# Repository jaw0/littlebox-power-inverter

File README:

google sponsored a contest, [the little box challenge,](https://www.littleboxchallenge.com)
to design a small, efficient, 2kVA power inverter.

this is what I came up with. it did not win.

* * * * * * * * WARNING * * * * * * * *

This device contains potentially lethal voltages.

This device does not comply with consumer grade
electrical safety requirements.

DO NOT USE OR BUILD THIS UNLESS YOU ARE FAMILIAR WITH
THE SAFETY PRECAUTIONS FOR WORKING WITH HIGH VOLTAGE.

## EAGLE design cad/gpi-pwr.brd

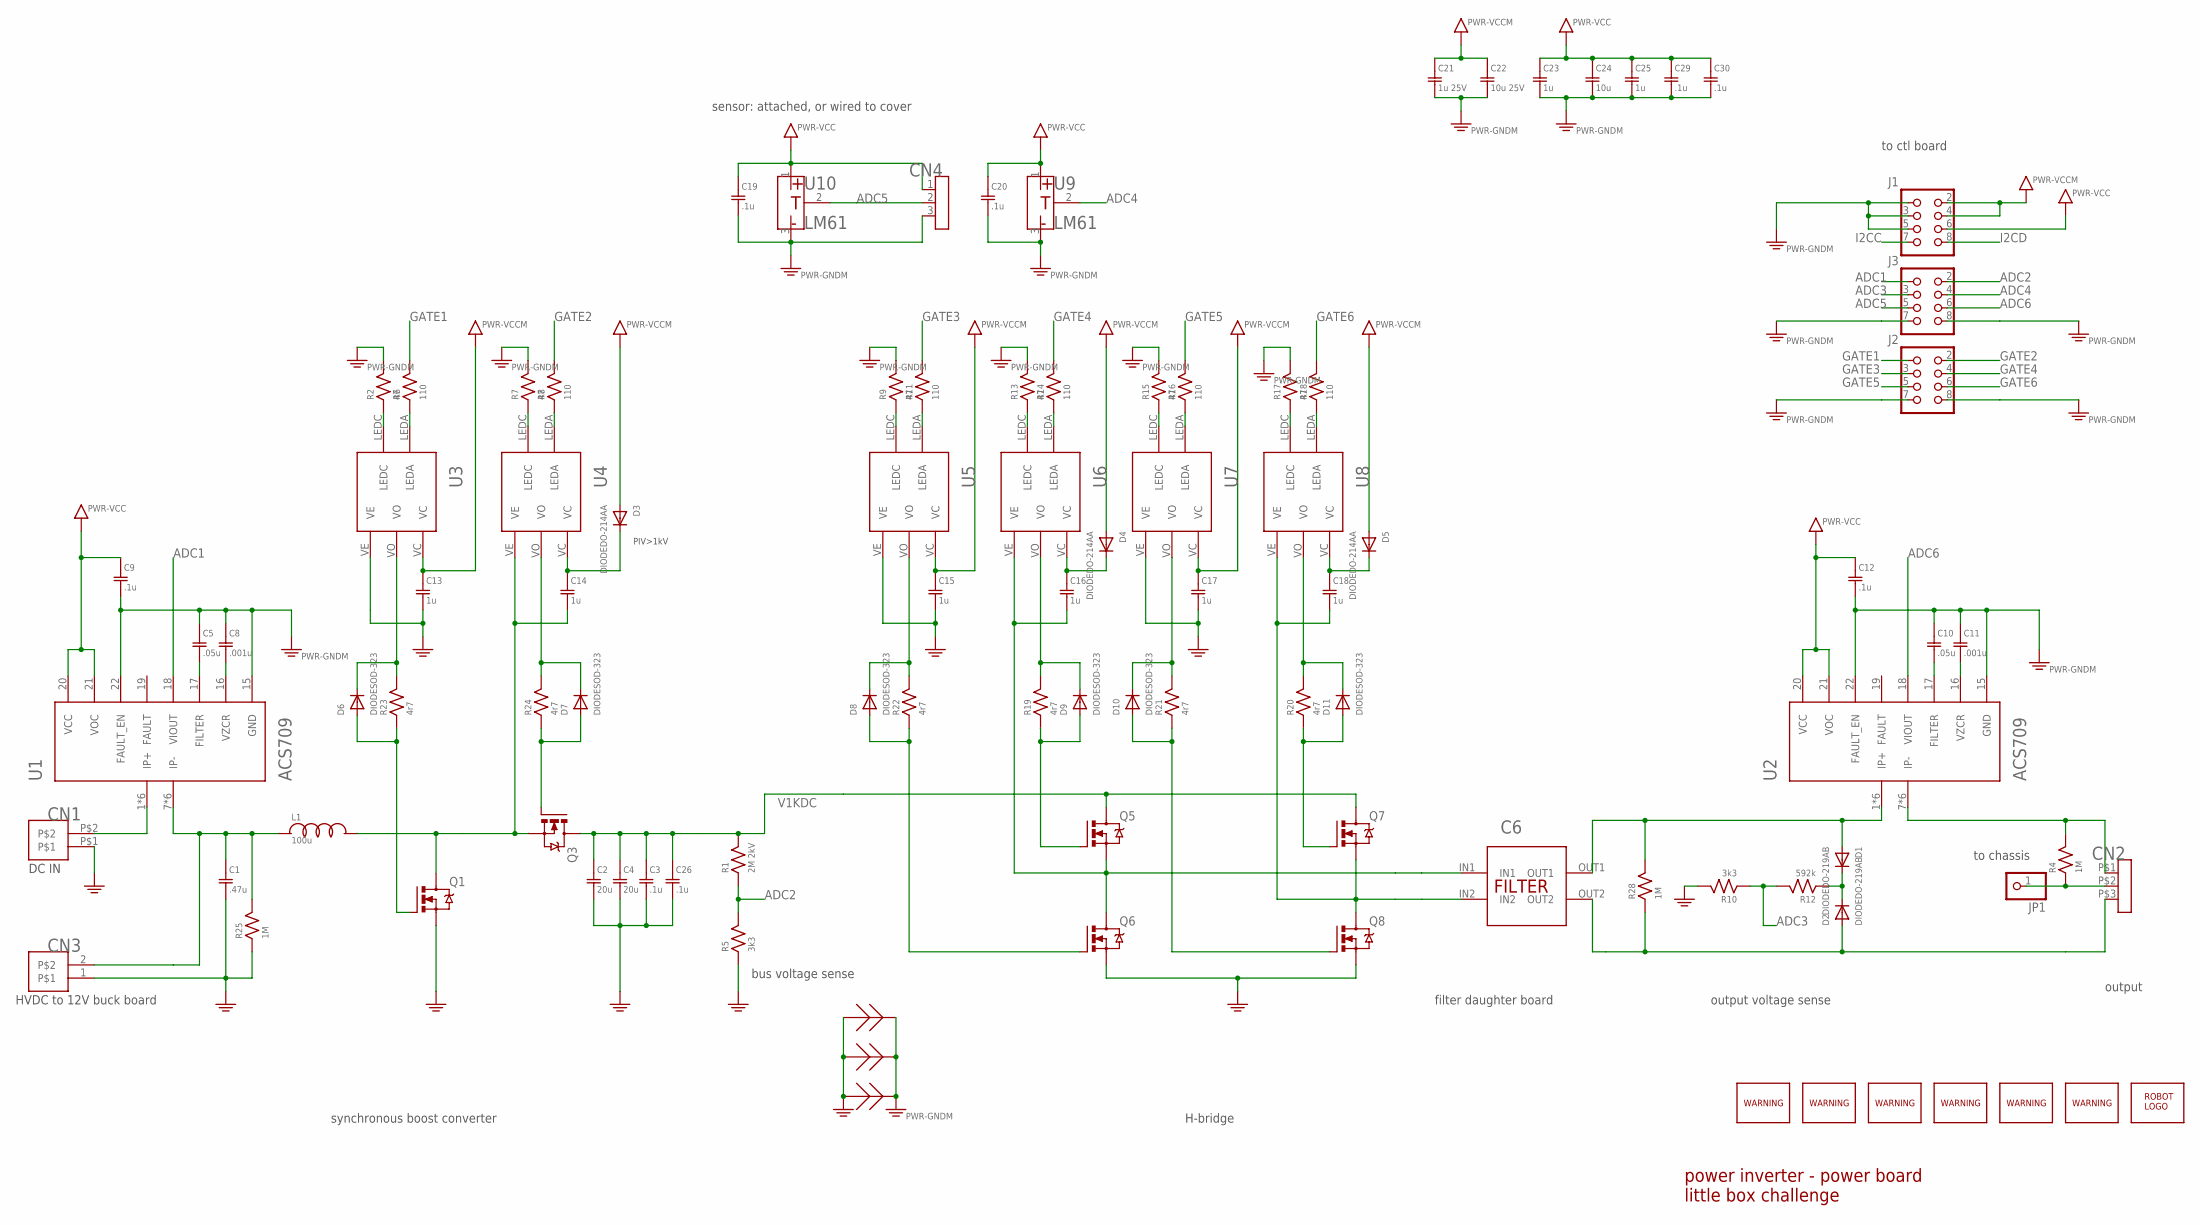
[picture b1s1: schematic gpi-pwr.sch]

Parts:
C1: .47u; R46KI333000N1M
C2, C4: 20u; MKP1848S62010JY5F
C3, C26: .1u; SMD2220
C5, C10: .05u; SMD0603
C6: FILTER; FILTER-B4R0
C8, C11: .001u; SMD0603
C9, C12, C19, C20, C29, C30: .1u; SMD0603
C13, C14, C15, C16, C17, C18, C23, C25: 1u; SMD0603
C21: 1u 25V; SMD0603
C22: 10u 25V; SMD0603
C24: 10u; SMD0603
CN1: HEADER-1X2; CONN-10AWG-2
CN2: HEADER-3X1; CONN-10AWG-3
CN3: HEADER-1X2.4; HEADER-1X2-THM-WIDE
CN4: HEADER-3X12MM; HEADER-3X1-2SMD
D1, D2: DIODEDO-219AB; DO-219AB
D3, D4, D5: DIODEDO-214AA; DO-214AA
D6, D7, D8, D9, D10, D11: DIODESOD-323; SOD-323
J1, J2, J3: HEADER-2X4; HEADER-2X04
JP1: PINHD-1X1; 1X01
L1: 100u; AIRD03
Q1, Q3, Q5, Q6, Q7, Q8: C2M0160120D; TO-247-3-DOWN
R1: 2M 2kV; SMD2512
R2, R7, R9, R13, R15, R17: 47; SMD0603
R4, R25, R28: 1M; SMD1206
R5, R10: 3k3; SMD0603
R6, R8, R11, R14, R16, R18: 110; SMD0603
R12: 592k; SMD1206
R19, R20, R21, R22, R23, R24: 4r7; SMD0508
U1, U2: ACS709; QSOP24
U3, U4, U5, U6, U7, U8: ACPL-P346P346; ACPL-P346
U9, U10: LM61; SOT-23
U$1: ROBOTMAN-LOGO
U$2, U$3, U$4, U$5, U$6, U$7: SYMBOL-WARNING
Z1, Z2, Z3: SHORT

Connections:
ADC1: J3.1, U1.18 (VIOUT)
ADC2: J3.2, R1.P$1, R5.2
ADC3: J3.3, R10.1, R12.2
ADC4: J3.4, U9.2 (OUT)
ADC5: CN4.2, J3.5, U10.2 (OUT)
ADC6: J3.6, U2.18 (VIOUT)
GATE1: J2.1, R6.2
GATE2: J2.2, R8.2
GATE3: J2.3, R11.2
GATE4: J2.4, R14.2
GATE5: J2.5, R16.2
GATE6: J2.6, R18.2
GND: C1.P$2, C2.2A, C2.2B, C3.P$2, C4.2A, C4.2B, C13.2, C15.2, C17.2, C26.P$2, CN1.P$1, CN3.1, Q1.3 (S), Q6.3 (S), Q8.3 (S), R5.1, R10.2, R25.1, U3.VE, U5.VE, U7.VE, Z1.P$1, Z2.P$1, Z3.P$1
GNDM: C5.1, C8.1, C9.2, C10.1, C11.1, C12.2, C19.2, C20.2, C21.2, C22.2, C23.2, C24.2, C25.2, C29.2, C30.2, CN4.3, J1.1, J1.3, J1.5, J2.7, J2.8, J3.7, J3.8, R2.2, R7.2, R9.2, R13.2, R15.2, R17.2, U1.15 (GND), U1.22 (FAULT_EN), U2.15 (GND), U2.22 (FAULT_EN), U9.3 (G), U10.3 (G), Z1.P$2, Z2.P$2, Z3.P$2
I2CC: J1.7
I2CD: J1.8
unnamed: CN1.P$2, U1.1 (IP+), U1.2 (IP+), U1.3 (IP+), U1.4 (IP+), U1.5 (IP+), U1.6 (IP+)
unnamed: D9.C, R19.P$2, U6.VO
unnamed: C14.2, L1.P$2, Q1.2 (D), Q3.3 (S), U4.VE
unnamed: D6.A, Q1.1 (G), R23.P$1
unnamed: D6.C, R23.P$2, U3.VO
unnamed: C1.P$1, CN3.2, L1.P$1, R25.2, U1.7 (IP-), U1.8 (IP-), U1.9 (IP-), U1.10 (IP-), U1.11 (IP-), U1.12 (IP-)
unnamed: D1.C, D2.C, R12.1
unnamed: CN2.P$1 (1), R4.2, U2.7 (IP-), U2.8 (IP-), U2.9 (IP-), U2.10 (IP-), U2.11 (IP-), U2.12 (IP-)
unnamed: CN2.P$2 (2), JP1.1, R4.1
unnamed: C5.2, U1.17 (FILTER)
unnamed: C8.2, U1.16 (VZCR)
unnamed: C10.2, U2.17 (FILTER)
unnamed: C6.IN1, C16.2, Q5.3 (S), Q6.2 (D), U6.VE
unnamed: C6.IN2, C18.2, Q7.3 (S), Q8.2 (D), U8.VE
unnamed: C11.2, U2.16 (VZCR)
unnamed: C14.1, D3.C, U4.VC
unnamed: D9.A, Q5.1 (G), R19.P$1
unnamed: D8.A, Q6.1 (G), R22.P$1
unnamed: D10.A, Q8.1 (G), R21.P$1
unnamed: D11.A, Q7.1 (G), R20.P$1
unnamed: R2.1, U3.LEDC
unnamed: C6.OUT1, D1.A, R28.2, U2.1 (IP+), U2.2 (IP+), U2.3 (IP+), U2.4 (IP+), U2.5 (IP+), U2.6 (IP+)
unnamed: C6.OUT2, CN2.P$3 (3), D2.A, R28.1
unnamed: C16.1, D4.C, U6.VC
unnamed: R6.1, U3.LEDA
unnamed: C18.1, D5.C, U8.VC
unnamed: R7.1, U4.LEDC
unnamed: R8.1, U4.LEDA
unnamed: R9.1, U5.LEDC
unnamed: R11.1, U5.LEDA
unnamed: R13.1, U6.LEDC
unnamed: R14.1, U6.LEDA
unnamed: R15.1, U7.LEDC
unnamed: R16.1, U7.LEDA
unnamed: R17.1, U8.LEDC
unnamed: R18.1, U8.LEDA
unnamed: D11.C, R20.P$2, U8.VO
unnamed: D8.C, R22.P$2, U5.VO
unnamed: D10.C, R21.P$2, U7.VO
unnamed: D7.C, R24.P$2, U4.VO
unnamed: D7.A, Q3.1 (G), R24.P$1
V1KDC: C2.1A, C2.1B, C3.P$1, C4.1A, C4.1B, C26.P$1, Q3.2 (D), Q5.2 (D), Q7.2 (D), R1.P$2
VCC: C9.1, C12.1, C19.1, C20.1, C23.1, C24.1, C25.1, C29.1, C30.1, CN4.1, J1.6, U1.20 (VCC), U1.21 (VOC), U2.20 (VCC), U2.21 (VOC), U9.1 (V), U10.1 (V)
VCCM: C13.1, C15.1, C17.1, C21.1, C22.1, D3.A, D4.A, D5.A, J1.2, J1.4, U3.VC, U5.VC, U7.VC

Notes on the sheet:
PIV>1kV
DC IN
HVDC to 12V buck board
to chassis
sensor: attached, or wired to cover
synchronous boost converter
H-bridge
output
output voltage sense
to ctl board
power inverter - power board little box challenge
filter daughter board
bus voltage sense

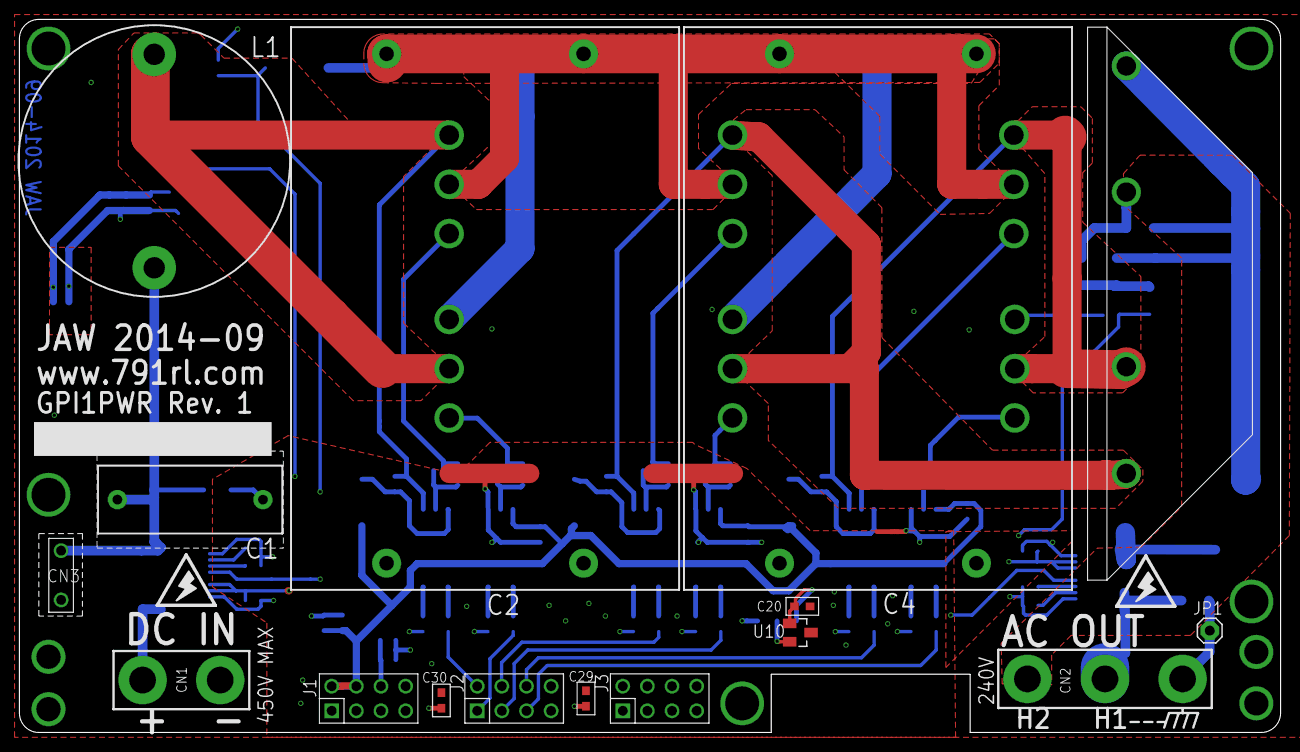
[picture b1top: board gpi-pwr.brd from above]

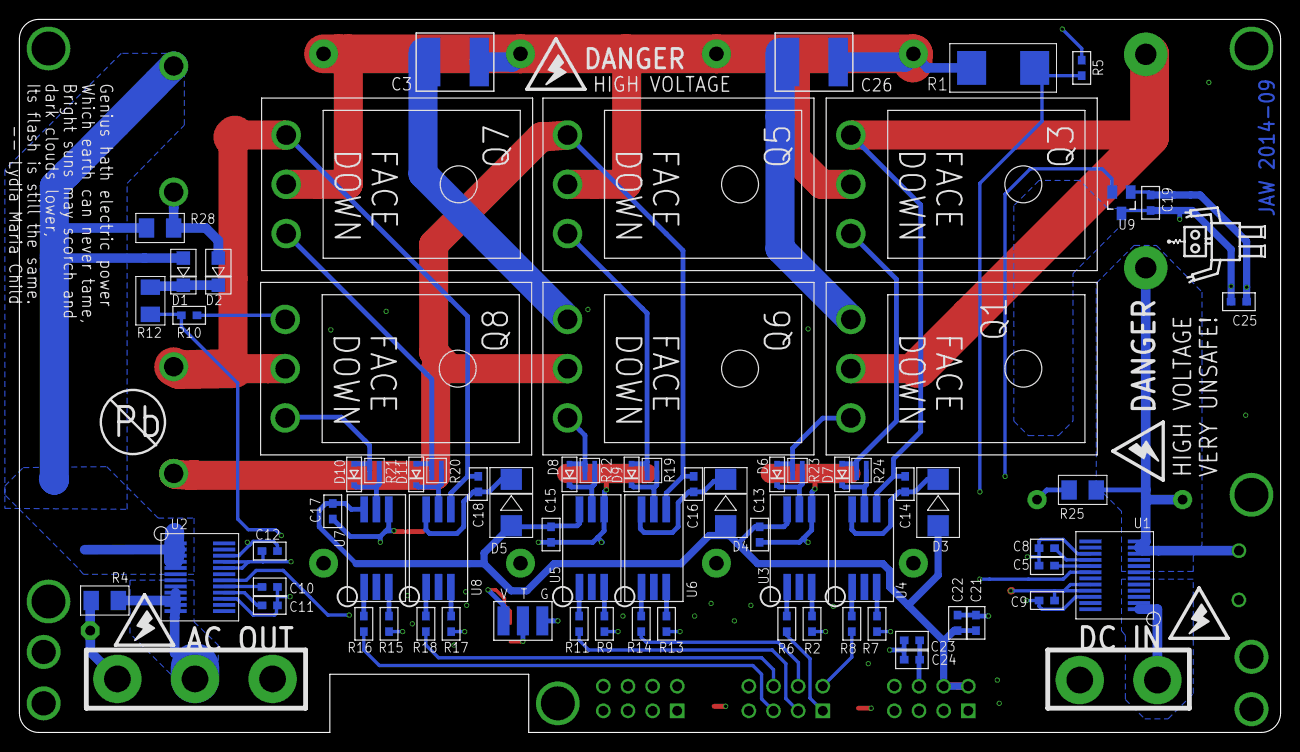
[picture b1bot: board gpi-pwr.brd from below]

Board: 4 copper layers, 130.0 x 73.5 mm, 98 parts (77 on the bottom side), 58 nets.

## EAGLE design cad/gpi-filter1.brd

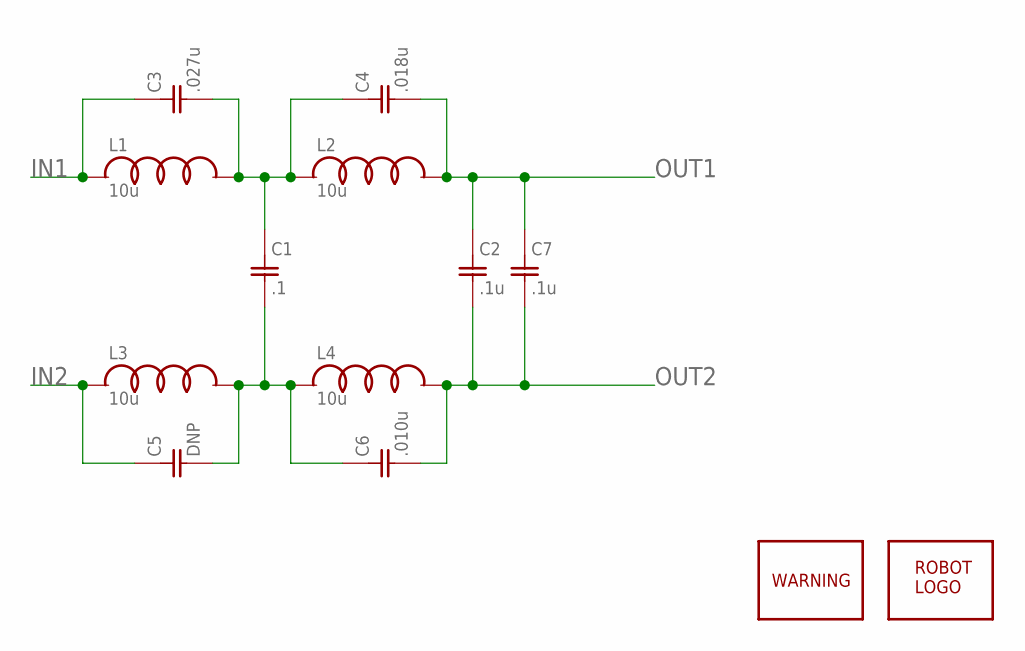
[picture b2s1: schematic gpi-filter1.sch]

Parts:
C1: .1; SMD1210
C2, C7: .1u; SMD1210
C3: .027u; SMD1210
C4: .018u; SMD1210
C5: DNP; SMD1210
C6: .010u; SMD1210
L1, L2, L3, L4: 10u; XAL10
U$1: ROBOTMAN-LOGO
U$2: SYMBOL-WARNING

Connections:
IN1: C3.1, L1.P$1
IN2: C5.1, L3.P$1
unnamed: C1.1, C3.2, C4.1, L1.P$2, L2.P$1
unnamed: C1.2, C5.2, C6.1, L3.P$2, L4.P$1
OUT1: C2.1, C4.2, C7.1, L2.P$2
OUT2: C2.2, C6.2, C7.2, L4.P$2

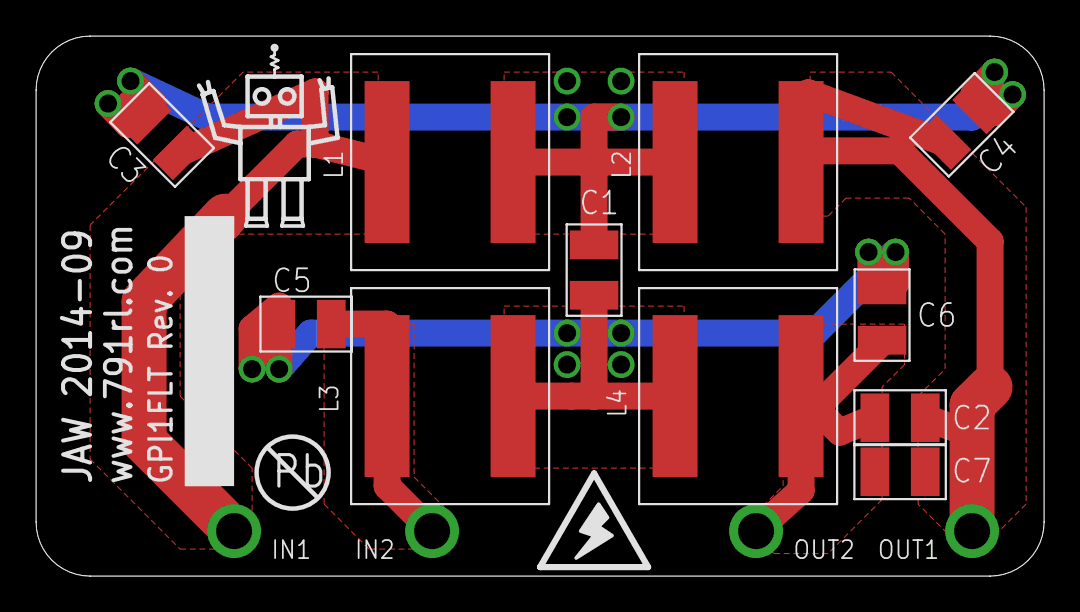
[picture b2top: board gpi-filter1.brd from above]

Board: 2 copper layers, 56.0 x 30.0 mm, 13 parts (0 on the bottom side), 6 nets.

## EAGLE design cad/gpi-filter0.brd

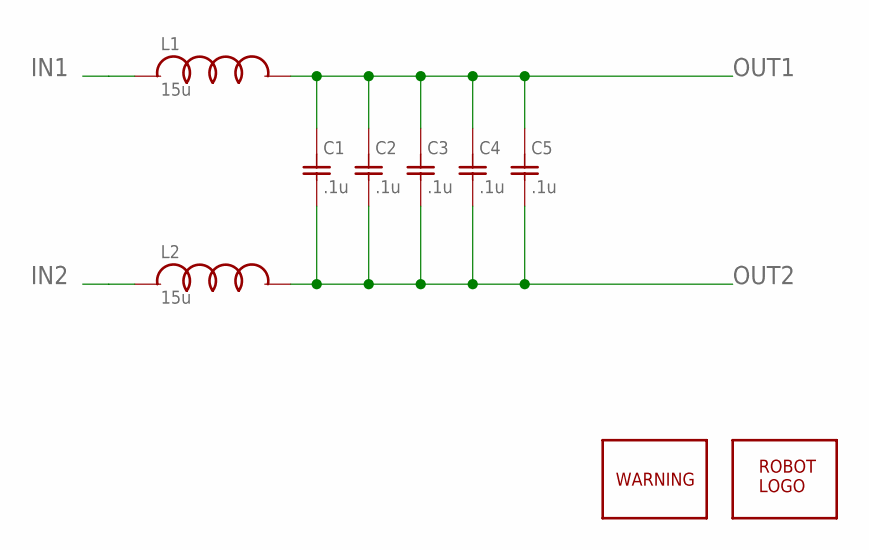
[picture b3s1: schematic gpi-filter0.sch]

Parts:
C1, C2, C3, C4, C5: .1u; SMD1210
L1, L2: 15u; BOURNS2303H
U$1: ROBOTMAN-LOGO
U$2: SYMBOL-WARNING

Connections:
IN1: L1.P$1
IN2: L2.P$1
OUT1: C1.1, C2.1, C3.1, C4.1, C5.1, L1.P$2
OUT2: C1.2, C2.2, C3.2, C4.2, C5.2, L2.P$2

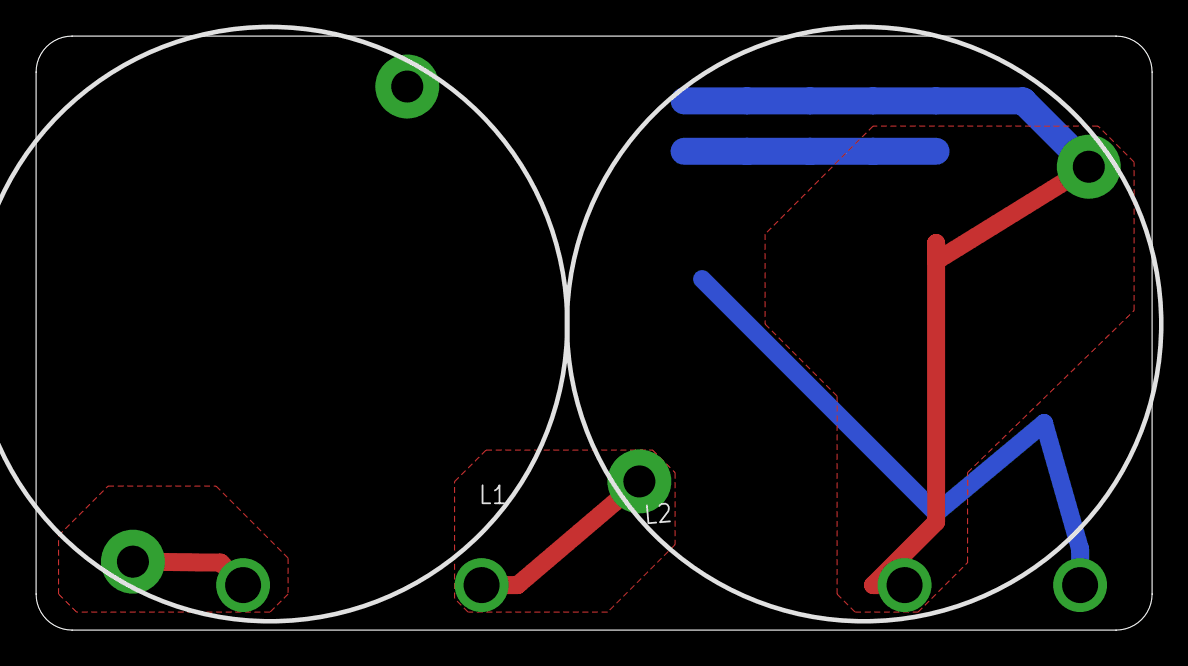
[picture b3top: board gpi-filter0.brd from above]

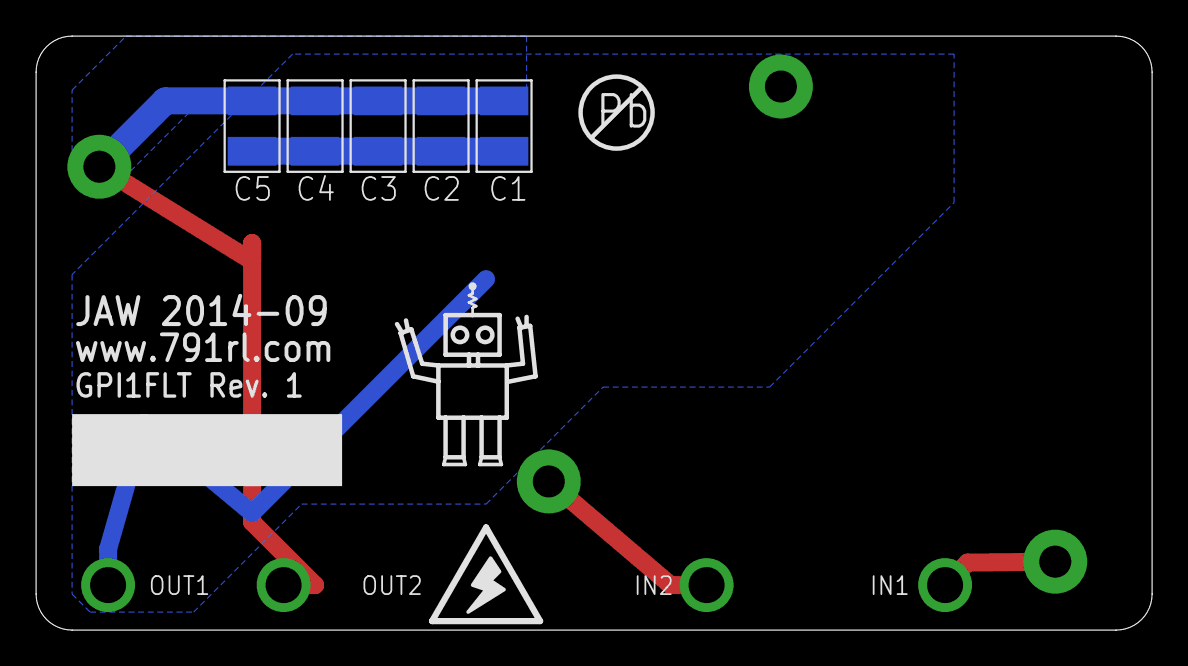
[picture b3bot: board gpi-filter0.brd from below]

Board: 2 copper layers, 62.0 x 33.0 mm, 9 parts (7 on the bottom side), 2 nets.

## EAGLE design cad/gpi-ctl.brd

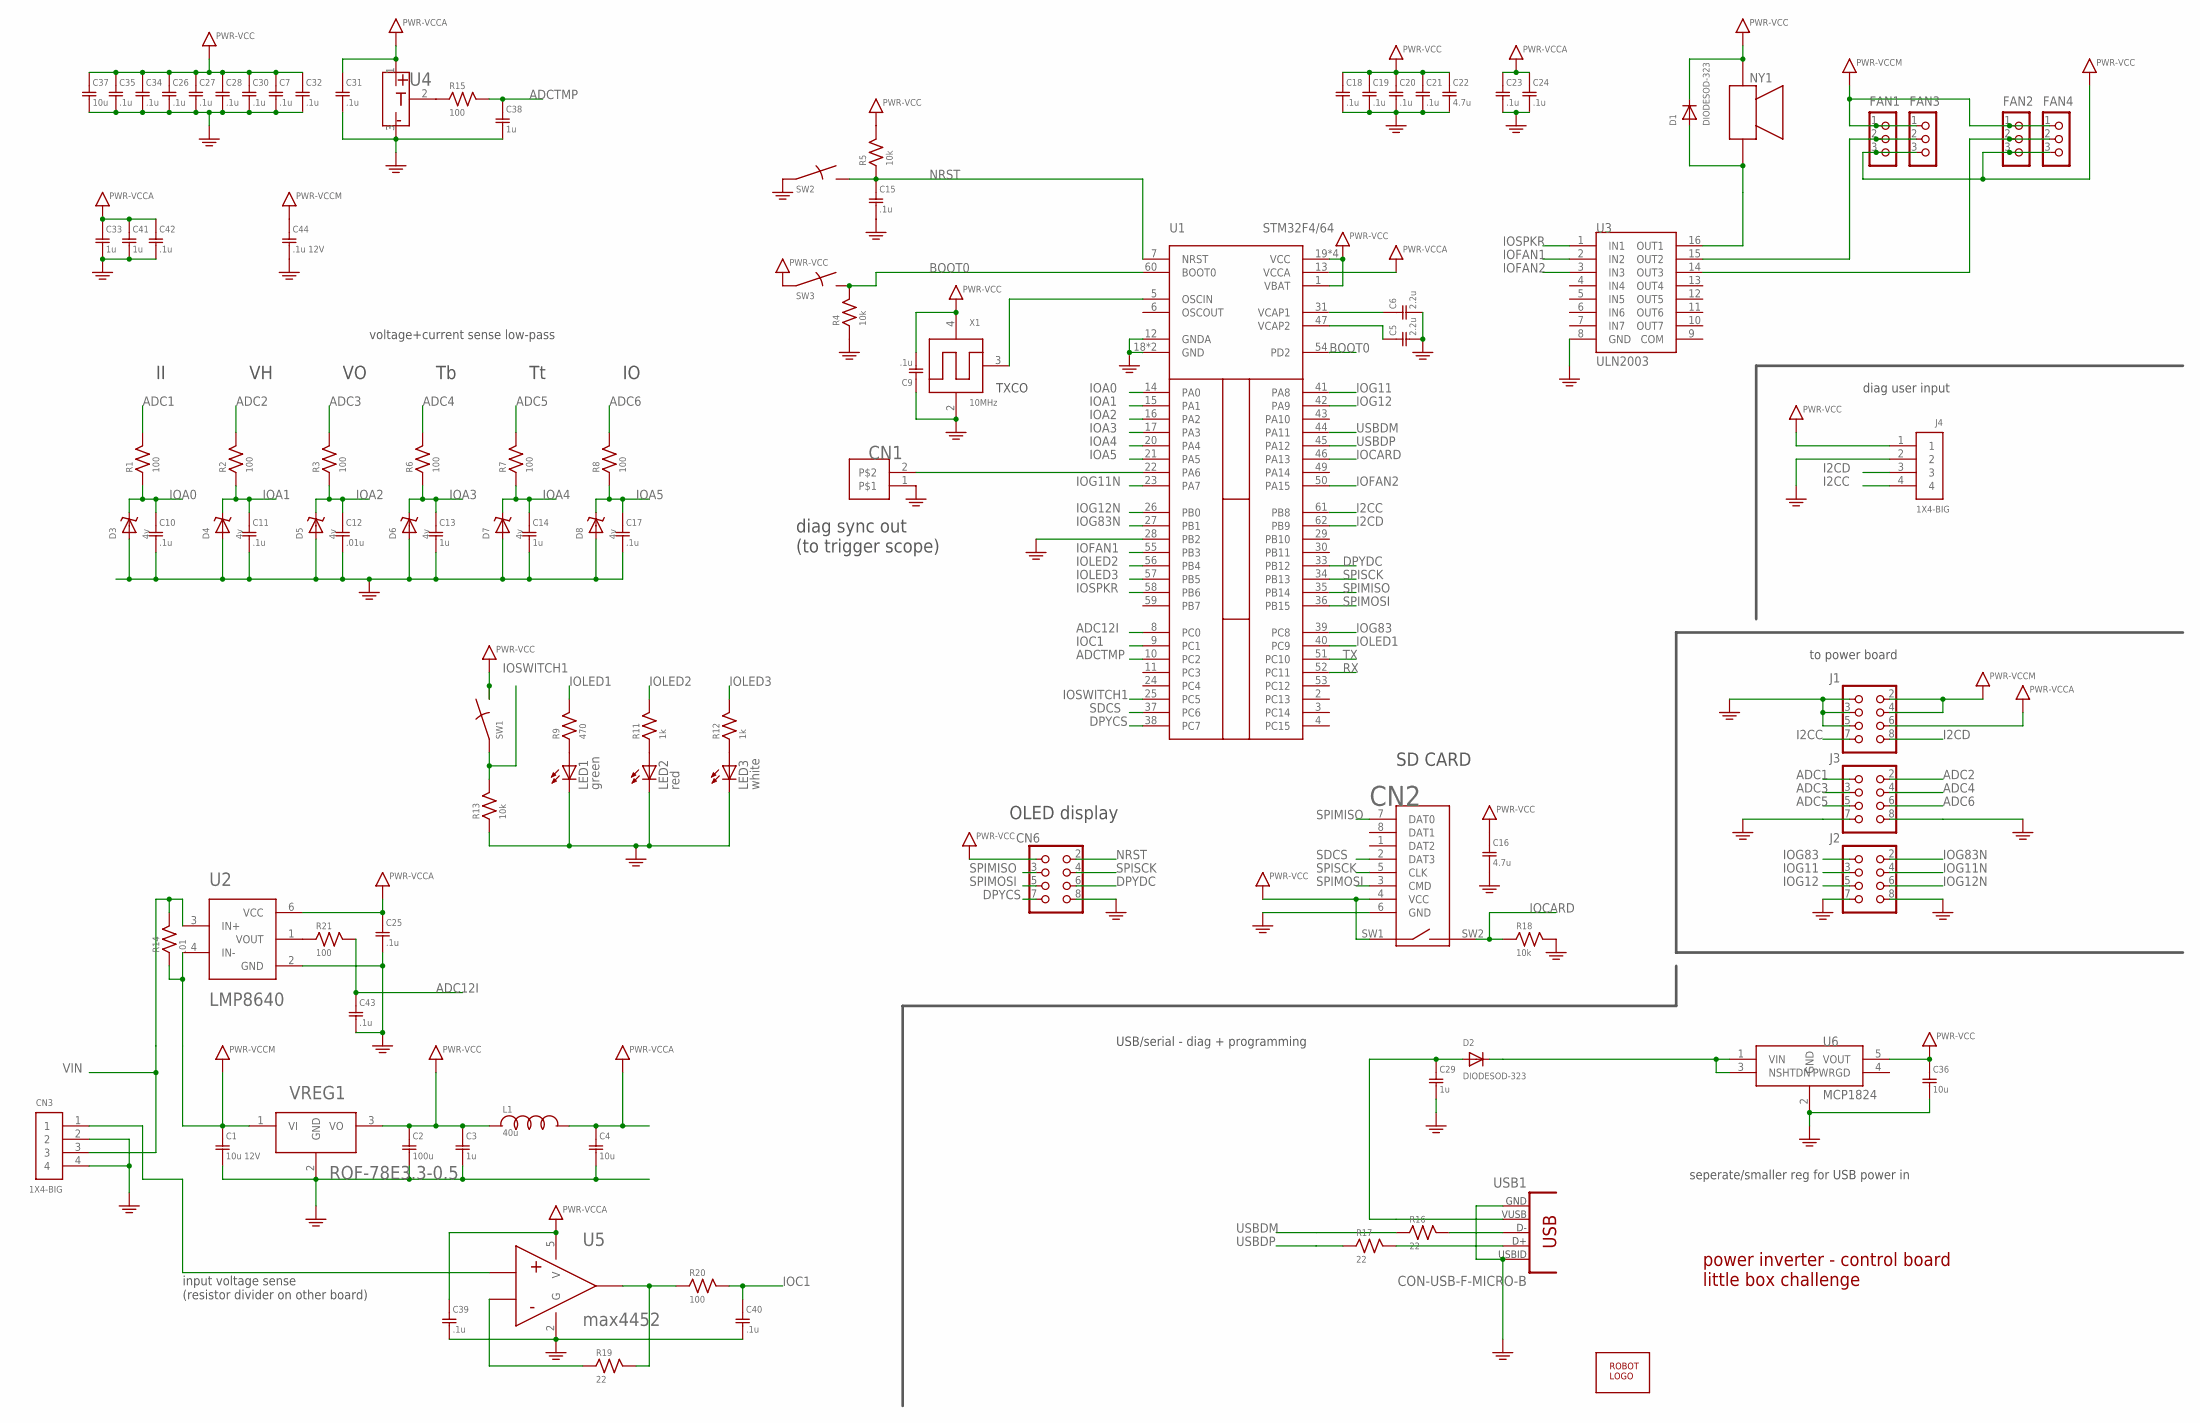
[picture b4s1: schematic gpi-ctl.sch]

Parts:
C1: 10u 12V; SMD0603
C2: 100u; SMD1210
C3, C13, C14, C29, C33, C38, C41: 1u; SMD0603
C4, C36, C37: 10u; SMD0603
C5, C6: 2.2u; SMD0603
C7, C9, C10, C11, C15, C17, C18, C19, C20, C21, C23, C24, C25, C26, C27, C28, C30, C31, C32, C34, C35, C39, C40, C42, C43: .1u; SMD0603
C12: .01u; SMD0603
C16, C22: 4.7u; SMD0603
C44: .1u 12V; SMD0603
CN1: HEADER-1X2.4; HEADER-1X2-THM-WIDE
CN2: MICROSDPLAIN; MICROSD/MOLEX/FRONT/PLAIN
CN3: 1X4-BIG; 1X04-BIG
CN6: HEADER-2X4; HEADER-2X04
D1, D2: DIODESOD-323; SOD-323
D3, D4, D5, D6, D7, D8: 4v; SOD-323
FAN1, FAN2, FAN3, FAN4: CON_HEADER_1X03-PTH; M1X3
J1, J2, J3: HEADER-2X4; HEADER-2X04
J4: 1X4-BIG; 1X04-BIG
L1: 40u; SMD0603
LED1: green; LED3MM
LED2: red; LED3MM
LED3: white; LED3MM
NY1: PUI-5040; PUI-0540
R1, R2, R3, R6, R7, R8, R15, R20, R21: 100; SMD0603
R4, R5, R13, R18: 10k; SMD0603
R9: 470; SMD0603
R11, R12: 1k; SMD0603
R14: .01; SMD0805
R16, R17, R19: 22; SMD0603
SW1: SWITCHGT12-THOLE; SWITCH-GT12MCBE
SW2, SW3: SWITCHKMR211; KMR211
U1: STM32F4/64; TQFP64
U2: LMP8640; SOT-6
U3: ULN2003; TSSOP-16
U4: TEMPERATURE; SOT-23
U5: max4452; SOT-23-5
U6: MCP1824; SOT-23-5
U$1: ROBOTMAN-LOGO
USB1: CON-USB-F-MICRO-B; CONN_USB_MICRO-B
VREG1: ROF-78E3.3-0.5; ROF7800
X1: 10MHz; OSC-AST3TQ

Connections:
ADC1: J3.1, R1.2
ADC2: J3.2, R2.2
ADC3: J3.3, R3.2
ADC4: J3.4, R6.2
ADC5: J3.5, R7.2
ADC6: J3.6, R8.2
ADC12I: C43.1, R21.2, U1.8 (PC0)
ADCTMP: C38.1, R15.2, U1.10 (PC2)
BOOT0: R4.2, SW3.2, SW3.4, U1.54 (PD2), U1.60 (BOOT0)
DPYCS: CN6.7, U1.38 (PC7)
DPYDC: CN6.6, U1.33 (PB12)
GND: C1.2, C2.2, C3.2, C4.2, C5.2, C6.2, C7.2, C9.1, C10.2, C11.2, C12.2, C13.2, C14.2, C15.2, C16.2, C17.2, C18.2, C19.2, C20.2, C21.2, C22.2, C23.2, C24.2, C25.2, C26.2, C27.2, C28.2, C29.2, C30.2, C31.2, C32.2, C33.2, C34.2, C35.2, C36.2, C37.2, C38.2, C39.2, C40.2, C41.2, C42.2, C43.2, C44.2, CN1.1, CN2.6 (GND), CN3.2, CN3.4, CN6.8, D3.A, D4.A, D5.A, D6.A, D7.A, D8.A, J1.1, J1.3, J1.5, J2.7, J2.8, J3.7, J3.8, J4.2, LED1.K (C), LED2.K (C), LED3.K (C), R4.1, R13.1, R18.2, SW2.1, SW2.3, U1.12 (GNDA), U1.18 (GND), U1.28 (PB2), U1.63 (GND), U2.2 (GND), U3.8 (GND), U4.3 (G), U5.2 (G), U6.2 (GND), USB1.P4 (USBID), USB1.P5 (GND), VREG1.2 (GND), X1.2 (GND)
I2CC: J1.7, J4.4, U1.61 (PB8)
I2CD: J1.8, J4.3, U1.62 (PB9)
IOA0: C10.1, D3.C, R1.1, U1.14 (PA0)
IOA1: C11.1, D4.C, R2.1, U1.15 (PA1)
IOA2: C12.1, D5.C, R3.1, U1.16 (PA2)
IOA3: C13.1, D6.C, R6.1, U1.17 (PA3)
IOA4: C14.1, D7.C, R7.1, U1.20 (PA4)
IOA5: C17.1, D8.C, R8.1, U1.21 (PA5)
IOC1: C40.1, R20.2, U1.9 (PC1)
IOCARD: CN2.SW2, R18.1, U1.46 (PA13)
IOFAN1: U1.55 (PB3), U3.2 (IN2)
IOFAN2: U1.50 (PA15), U3.3 (IN3)
IOG11: J2.3, U1.41 (PA8)
IOG11N: J2.4, U1.23 (PA7)
IOG12: J2.5, U1.42 (PA9)
IOG12N: J2.6, U1.26 (PB0)
IOG83: J2.1, U1.39 (PC8)
IOG83N: J2.2, U1.27 (PB1)
IOLED1: R9.2, U1.40 (PC9)
IOLED2: R11.2, U1.56 (PB4)
IOLED3: R12.2, U1.57 (PB5)
IOSPKR: U1.58 (PB6), U3.1 (IN1)
IOSWITCH1: R13.2, SW1.1, U1.25 (PC5)
unnamed: FAN2.2, FAN4.2, U3.14 (OUT3)
unnamed: R17.2, USB1.P3 (D+)
unnamed: U1.5 (OSCIN), X1.3 (OSC)
unnamed: R16.2, USB1.P2 (D-)
unnamed: FAN1.2, FAN3.2, U3.15 (OUT2)
unnamed: D2.C, U6.1 (VIN), U6.3 (NSHTDN)
unnamed: R15.1, U4.2 (OUT)
unnamed: R19.1, U5.4 (INM)
unnamed: R19.2, R20.1, U5.1 (OUT)
unnamed: CN1.2, U1.22 (PA6)
unnamed: CN3.1, U5.3 (INP)
unnamed: LED1.A, R9.1
unnamed: LED2.A, R11.1
unnamed: LED3.A, R12.1
unnamed: R21.1, U2.1 (VOUT)
unnamed: C6.1, U1.31 (VCAP1)
unnamed: C5.1, U1.47 (VCAP2)
NRST: C15.1, CN6.2, R5.1, SW2.2, SW2.4, U1.7 (NRST)
RX: U1.52 (PC11)
SDCS: CN2.2 (DAT3), U1.37 (PC6)
SPIMISO: CN2.7 (DAT0), CN6.3, U1.35 (PB14)
SPIMOSI: CN2.3 (CMD), CN6.5, U1.36 (PB15)
SPISCK: CN2.5 (CLK), CN6.4, U1.34 (PB13)
SPKR: D1.A, NY1.P2, U3.16 (OUT1)
TX: U1.51 (PC10)
USBDM: R16.1, U1.44 (PA11)
USBDP: R17.1, U1.45 (PA12)
VBUS: C29.1, D2.A, USB1.P1 (VUSB)
VCC: C2.1, C3.1, C7.1, C9.2, C16.1, C18.1, C19.1, C20.1, C21.1, C22.1, C26.1, C27.1, C28.1, C30.1, C32.1, C34.1, C35.1, C36.1, C37.1, CN2.4 (VCC), CN2.SW1, CN6.1, D1.C, FAN1.3, FAN2.3, FAN3.3, FAN4.3, J4.1, L1.1, NY1.P1, R5.2, SW1.3, SW3.1, SW3.3, U1.1 (VBAT), U1.19 (VCC), U1.32 (VCC), U1.48 (VCC), U1.64 (VCC), U6.5 (VOUT), VREG1.3 (VO), X1.4 (VCC)
VCCA: C4.1, C23.1, C24.1, C25.1, C31.1, C33.1, C39.1, C41.1, C42.1, J1.6, L1.2, U1.13 (VCCA), U2.6 (VCC), U4.1 (V), U5.5 (V)
VCCM: C1.1, C44.1, FAN1.1, FAN2.1, FAN3.1, FAN4.1, J1.2, J1.4, R14.1, U2.4 (IN-), VREG1.1 (VI)
VIN: CN3.3, R14.2, U2.3 (IN+)

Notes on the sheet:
OLED display
SD CARD
diag sync out (to trigger scope)
voltage+current sense low-pass
TXCO
input voltage sense (resistor divider on other board)
diag user input
to power board
seperate/smaller reg for USB power in
USB/serial - diag + programming
power inverter - control board little box challenge

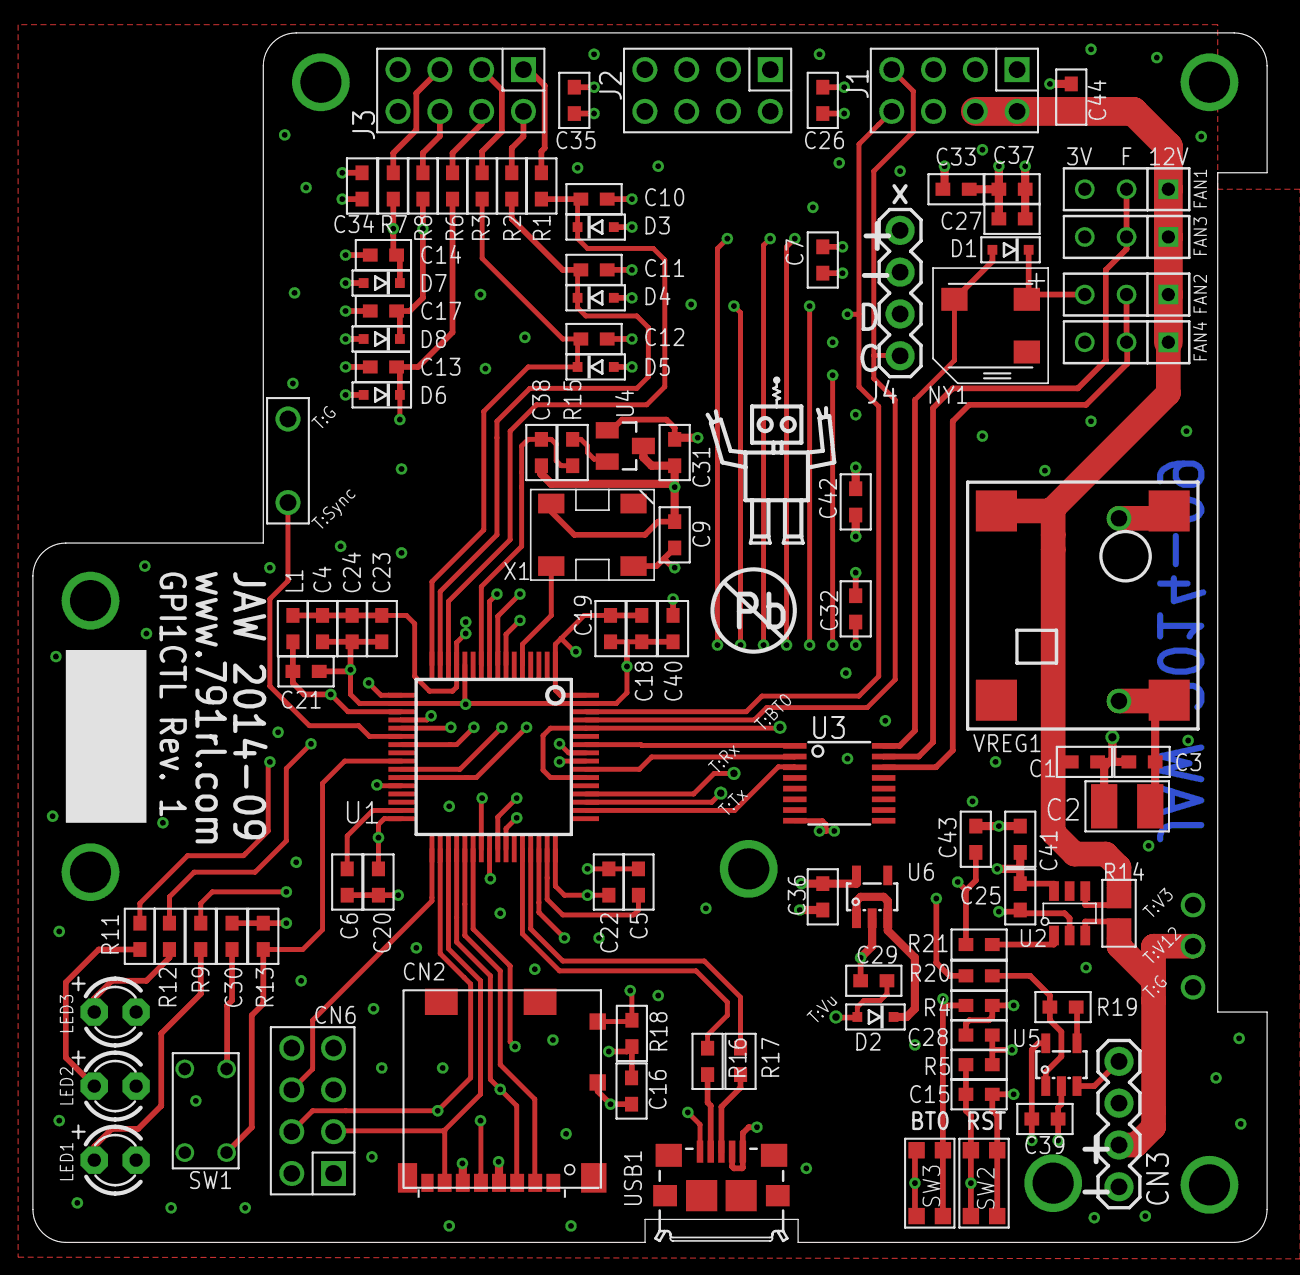
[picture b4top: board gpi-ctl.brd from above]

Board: 4 copper layers, 75.0 x 73.5 mm, 101 parts (0 on the bottom side), 65 nets.

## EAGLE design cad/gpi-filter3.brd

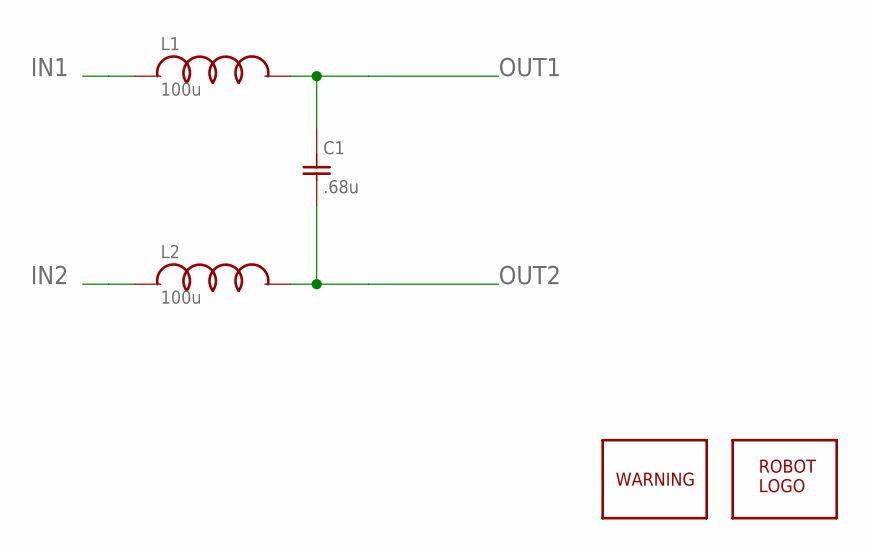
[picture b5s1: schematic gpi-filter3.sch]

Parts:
C1: .68u; R46KI36804P1M
L1, L2: 100u; AIRD03
U$1: ROBOTMAN-LOGO
U$2: SYMBOL-WARNING

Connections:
IN1: L1.P$1
IN2: L2.P$1
OUT1: C1.P$1, L1.P$2
OUT2: C1.P$2, L2.P$2

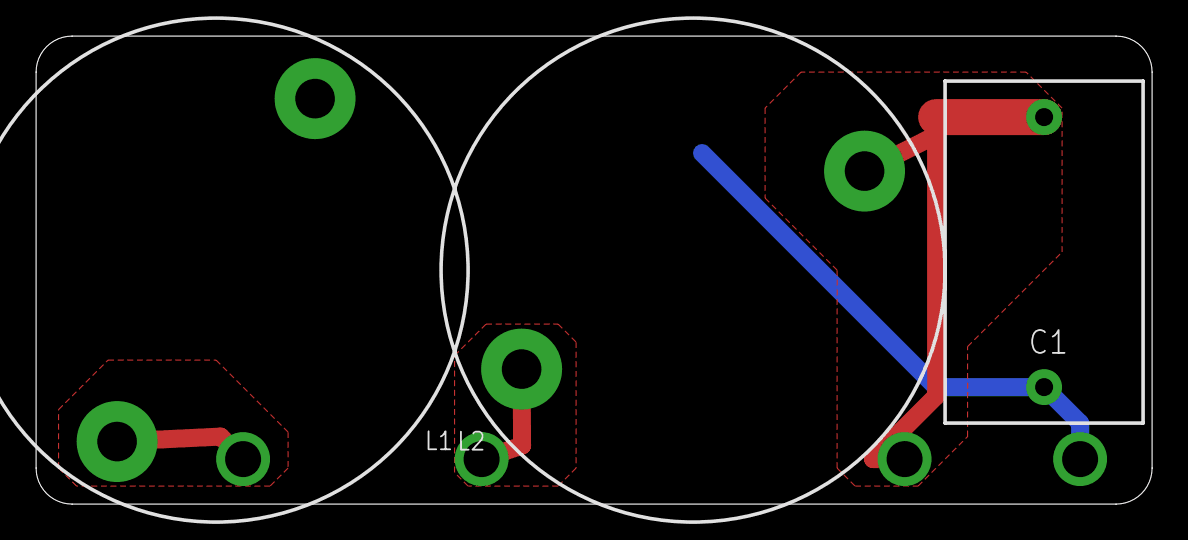
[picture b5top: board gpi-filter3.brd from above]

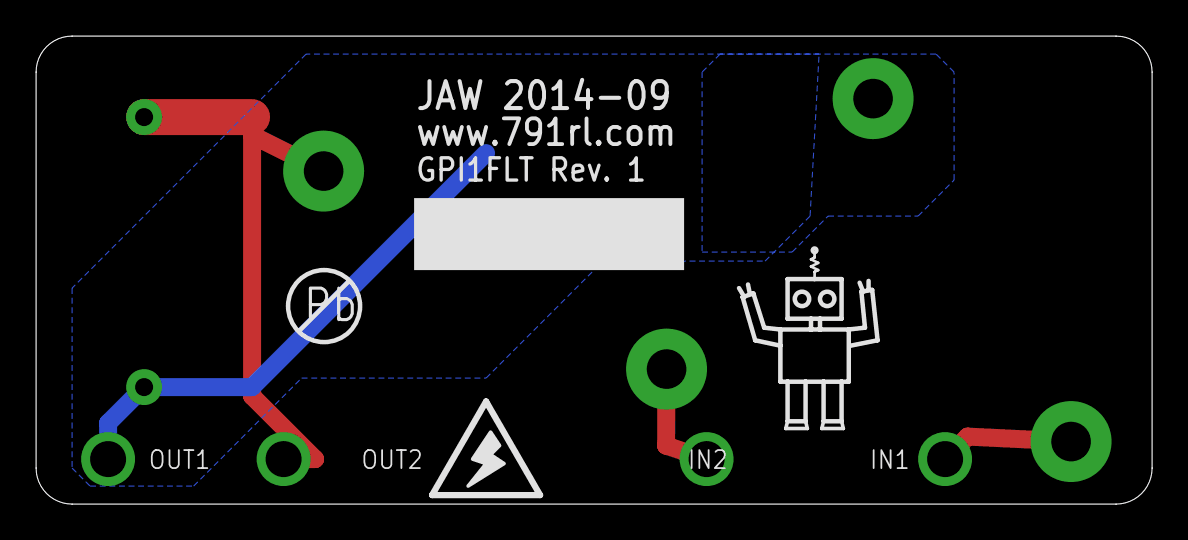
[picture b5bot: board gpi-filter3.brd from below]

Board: 2 copper layers, 62.0 x 26.0 mm, 5 parts (2 on the bottom side), 2 nets.

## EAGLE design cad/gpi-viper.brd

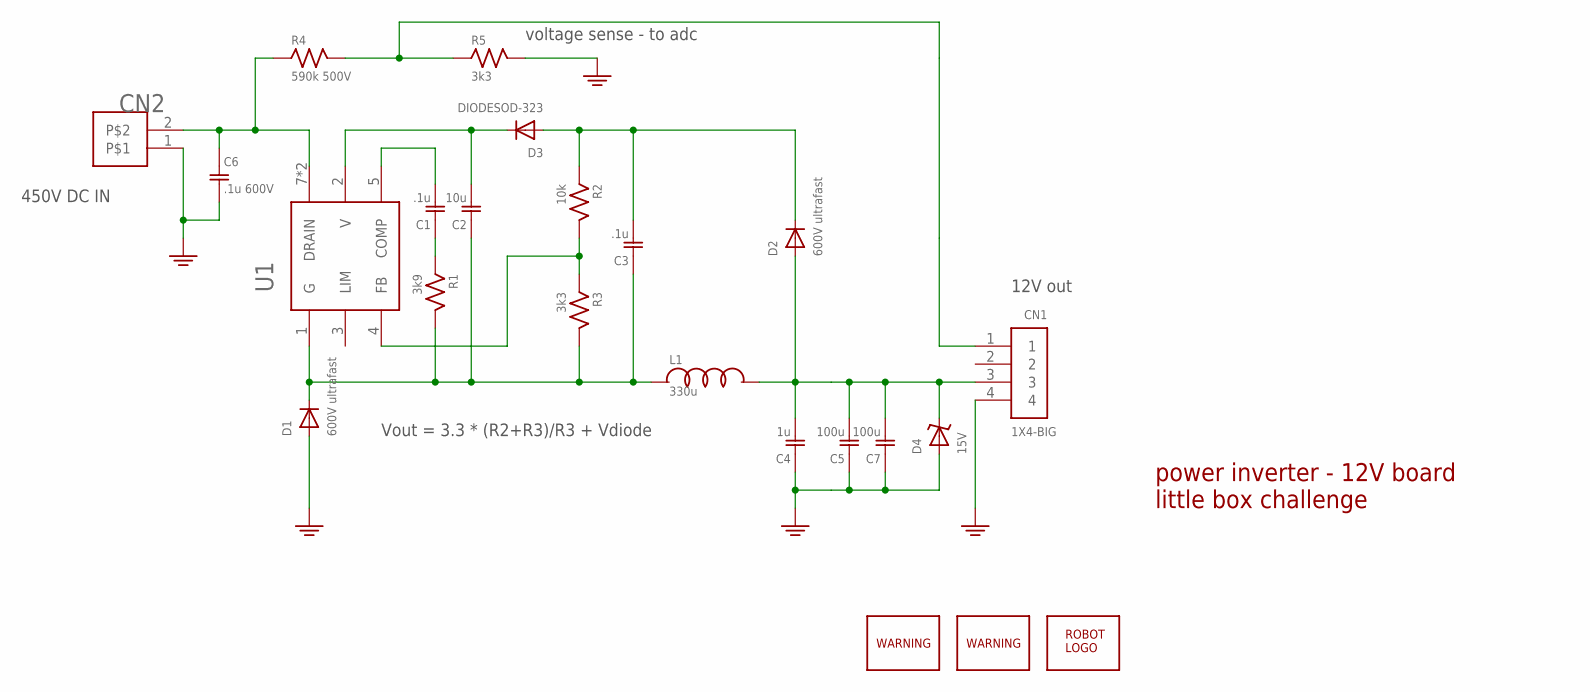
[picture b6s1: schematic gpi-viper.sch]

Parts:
C1, C3: .1u; SMD0603
C2: 10u; SMD0603
C4: 1u; SMD0603
C5, C7: 100u; SMD1210
C6: .1u 600V; SMD1210
CN1: 1X4-BIG; 1X04-BIG
CN2: HEADER-1X2.4; HEADER-1X2-THM-WIDE
D1, D2: 600V ultrafast; DO-214AC
D3: DIODESOD-323; SOD-323
D4: 15V; SOD-323@1
L1: 330u; BOURNS2100
R1: 3k9; SMD0603
R2: 10k; SMD0603
R3, R5: 3k3; SMD0603
R4: 590k 500V; SMD1206
U1: VIPER26DIP7; VIPER26-P7
U$1: ROBOTMAN-LOGO
U$2, U$3: SYMBOL-WARNING

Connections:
GND: C4.1, C5.1, C6.2, C7.1, CN1.4, CN2.1, D1.A, D4.A, R5.2
unnamed: C1.1, R1.1
unnamed: C2.1, C3.1, D1.C, L1.P$1, R1.2, R3.2, U1.1 (G)
unnamed: C1.2, U1.5 (COMP)
unnamed: C2.2, D3.C, U1.2 (V)
unnamed: C3.2, D2.C, D3.A, R2.1
unnamed: R2.2, R3.1, U1.4 (FB)
unnamed: C6.1, CN2.2, R4.1, U1.7 (DRAIN), U1.8 (DRAIN)
unnamed: CN1.1, R4.2, R5.1
VOUT: C4.2, C5.2, C7.2, CN1.3, D2.A, D4.C, L1.P$2

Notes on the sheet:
450V DC IN
Vout = 3.3 * (R2+R3)/R3 + Vdiode
12V out
power inverter - 12V board little box challenge
voltage sense - to adc
